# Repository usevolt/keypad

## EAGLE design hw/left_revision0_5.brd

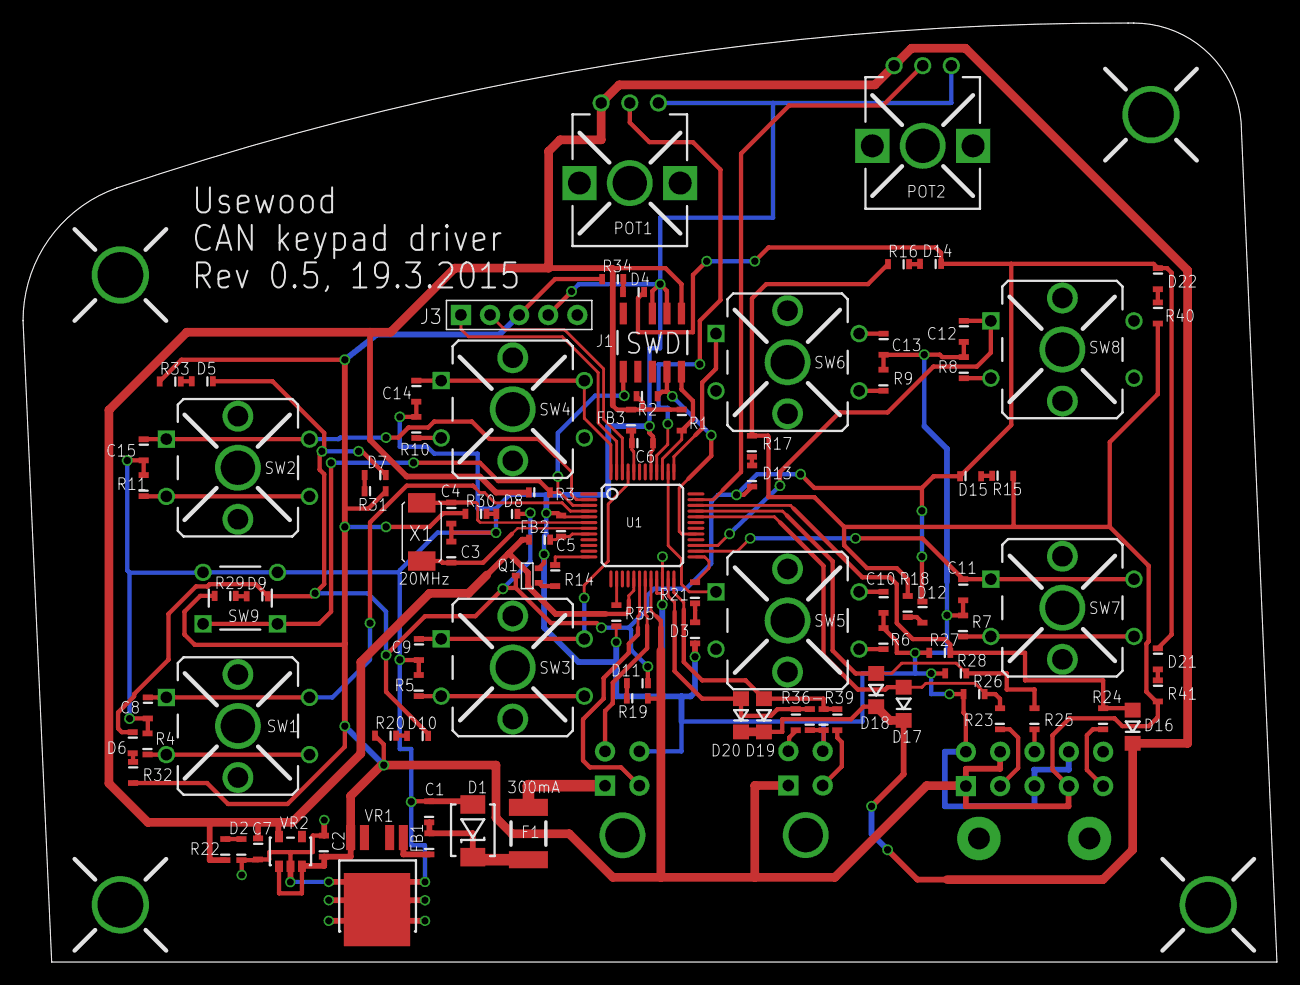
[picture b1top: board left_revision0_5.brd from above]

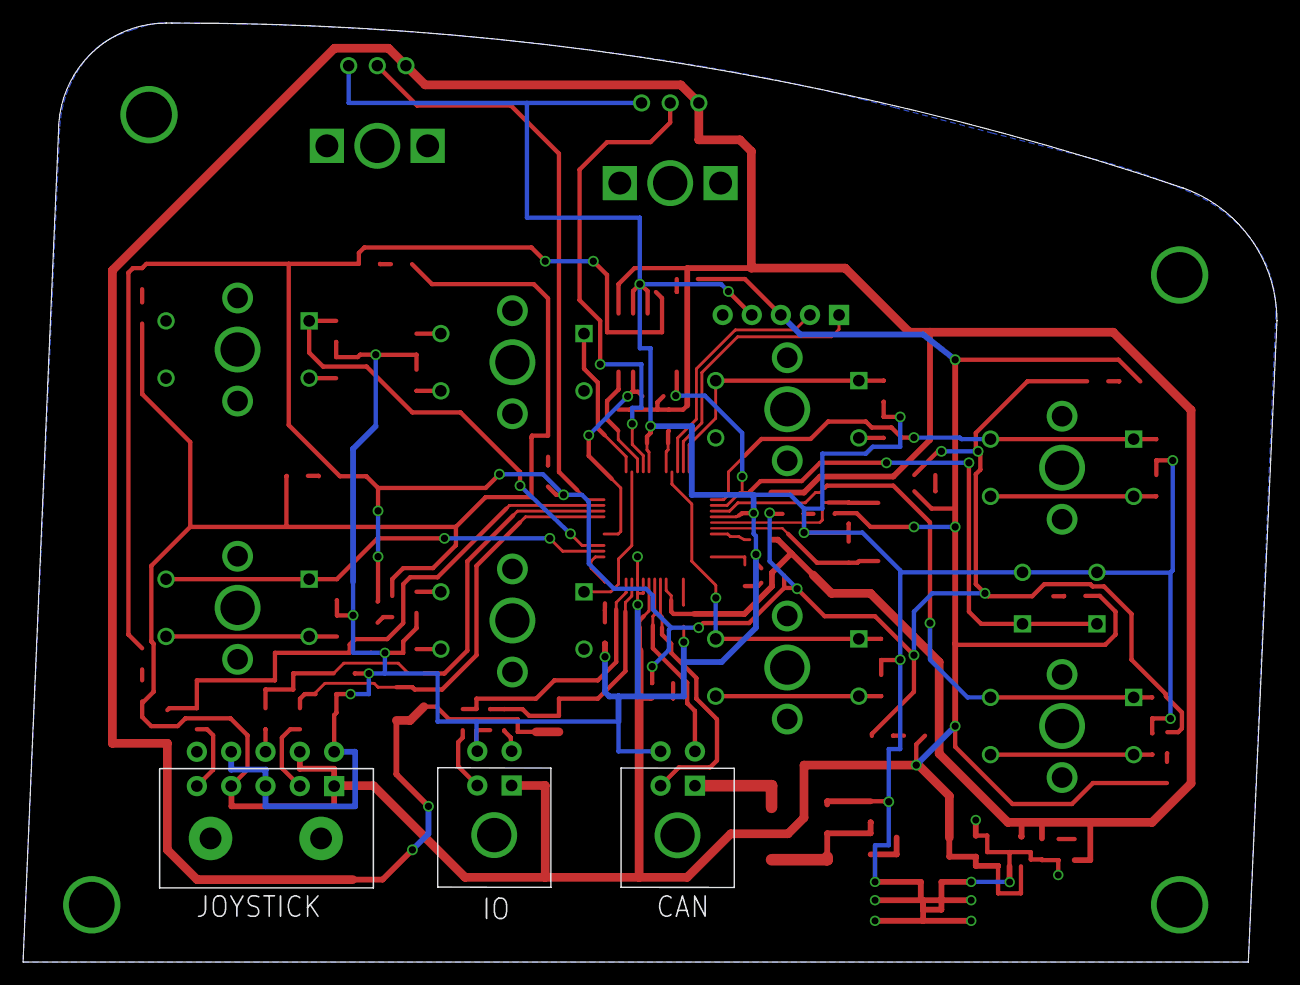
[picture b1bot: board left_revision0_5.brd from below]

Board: 2 copper layers, 109.5 x 82.0 mm, 101 parts (3 on the bottom side), 66 nets.

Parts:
C1, C2, C7: 1u; 0603
C3, C4: 15p; 0603
C5, C6, C8, C9, C10, C11, C12, C13, C14, C15: 100n; 0603
D1: DO-214AB
D2, D3, D4, D5, D6, D7, D8, D9, D10, D11, D12, D13, D14, D15, D21, D22: 0603
D16, D17, D18, D19, D20: DIODEDO219AB; DO219AB
F1: 300mA; FUSE_100MA
FB1, FB2, FB3: FERRITE0603; 0603
J1: SWD; ARM_10_PIN_JTAG/SWD_CONNECTOR
J2: CAN; MOLEX_MICRO-FIT_4WAY
J3: UART; HEADER5_1
J4: IO; MOLEX_MICRO-FIT_4WAY
Q1: SOT323
R1, R2, R3, R23, R24, R25, R36, R37: 10k; 0603
R4, R5, R6, R7, R8, R9, R10, R11: 100; 0603
R12, R13: 10k; RES_POT_RK09K1130C94
R14: 1k; 0603
R15, R16, R17, R18, R19, R20, R21, R29, R30, R31, R32, R33, R34: 470; 0603
R22: 430; 0603
R26, R27, R28, R38, R39: 20k; 0603
R35: 10; 0603
R40, R41: 0603
SW1, SW2, SW3, SW4, SW5, SW6, SW7, SW8: SWITCH_12X12MM_CENTER_HOLE
SW9: SWITCH_REGULAR
U1: QFP48
U$1: JOYSTICK; MOLEX-MICRO-FIT_10WAY
VR1: 175AA
VR2: SOP5
X1: 20MHz; XTAL_SMD_5X3.2

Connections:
+3V3: C7.1, D16.P$2, D17.P$2, D18.P$2, D19.P$2, D20.P$2, FB2.0, FB3.0, J1.P$1, R1.1, R2.1, R3.1, R12.P$3, R13.P$3, R22.1, U1.P$17, VR2.5
+5V: C2.1, J3.P$3, J4.P$1, R15.0, R16.0, R17.0, R18.0, R19.0, R20.0, R29.0, R30.0, R31.0, R32.0, R33.0, R34.0, R40.0, R41.0, U1.P$20, U$1.P$1, U$1.P$4, U$1.P$7, VR1.5, VR2.1, VR2.3
AD0: D17.P$1, R23.0, R26.1, U1.P$32
AD1: D18.P$1, R25.0, R28.1, U1.P$33
AD2: D16.P$1, R24.0, R27.1, U1.P$34
CANH: J2.P$3, U1.P$19
CANL: J2.P$2, U1.P$18
CAN_ISP: R35.0, U1.P$14
GND: C1.0, C2.0, C3.0, C4.0, C5.0, C6.0, C7.0, C8.0, C9.0, C10.0, C11.0, C12.0, C13.0, C14.0, C15.0, D1.P$1, D2.1, D3.1, J1.P$3, J1.P$5, J2.P$4, J3.P$4, J4.P$4, Q1.R, R4.0, R5.0, R6.0, R7.0, R8.0, R9.0, R10.0, R11.0, R12.P$1, R13.P$1, R26.0, R27.0, R28.0, R35.1, R38.1, R39.1, SW9.P$3, SW9.P$4, U1.P$5, U1.P$21, U1.P$22, U1.P$41, U$1.P$3, U$1.P$6, U$1.P$9, VR1.GND, VR2.2
IO1: D20.P$1, R37.1, R38.0, U1.P$23
IO2: D19.P$1, R36.1, R39.0, U1.P$24
LED3: D3.0, R21.1
LED4: D4.0, R34.1
LED5: D5.0, R33.1
LED6: D6.0, R32.1
LED7: D7.0, R31.1
LED8: D8.0, R30.1
LED9: D9.0, R29.1
unnamed: C1.1, D1.P$2, F1.P$2, FB1.0
unnamed: C6.1, FB3.1, U1.P$44
unnamed: D2.0, R22.0
unnamed: FB1.1, VR1.1
unnamed: R14.1, U1.P$12
unnamed: R21.0, U1.P$25
unnamed: R4.1, SW1.P$3, SW1.P$4
unnamed: R5.1, SW3.P$3, SW3.P$4
unnamed: R6.1, SW5.P$3, SW5.P$4
unnamed: R11.1, SW2.P$3, SW2.P$4
unnamed: R9.1, SW6.P$3, SW6.P$4
unnamed: R10.1, SW4.P$3, SW4.P$4
unnamed: R8.1, SW8.P$3, SW8.P$4
unnamed: R7.1, SW7.P$3, SW7.P$4
unnamed: D15.0, R15.1
unnamed: D14.0, R16.1
unnamed: D13.0, R17.1
unnamed: D12.0, R18.1
unnamed: D11.0, R19.1
unnamed: D10.0, R20.1
unnamed: C5.1, FB2.1, U1.P$8
unnamed: J4.P$2, R36.0
unnamed: J4.P$3, R37.0
unnamed: D21.0, R41.1
unnamed: D22.0, R40.1
unnamed: D4.1, D5.1, D6.1, D7.1, D8.1, D9.1, D10.1, D11.1, D12.1, D13.1, D14.1, D15.1, D21.1, D22.1, Q1.M
PIO1_2: R12.P$2, U1.P$40
PIO1_4: R13.P$2, U1.P$35
Q1: Q1.L, R14.0
RESET: J1.P$9, R3.0, SW9.P$1, SW9.P$2, U1.P$3
RXD: J3.P$2, U1.P$46
SW1: C8.1, SW1.P$1, SW1.P$2, U1.P$4
SW2: C15.1, SW2.P$1, SW2.P$2, U1.P$2
SW3: C9.1, SW3.P$1, SW3.P$2, U1.P$45
SW4: C14.1, SW4.P$1, SW4.P$2, U1.P$48
SW5: C10.1, SW5.P$1, SW5.P$2, U1.P$38
SW6: C13.1, SW6.P$1, SW6.P$2, U1.P$37
SW7: C11.1, SW7.P$1, SW7.P$2, U1.P$26
SW8: C12.1, SW8.P$1, SW8.P$2, U1.P$27
SWDCLK: J1.P$4, R2.0, U1.P$29
SWDIO: J1.P$2, R1.0, U1.P$39
TXD: J3.P$1, U1.P$47
VDD: F1.P$1, J2.P$1
XJOY: R23.1, U$1.P$2
XTALIN: C4.1, U1.P$6, X1.P$2
XTALOUT: C3.1, U1.P$7, X1.P$1
YJOY: R24.1, U$1.P$5
ZJOY: R25.1, U$1.P$8

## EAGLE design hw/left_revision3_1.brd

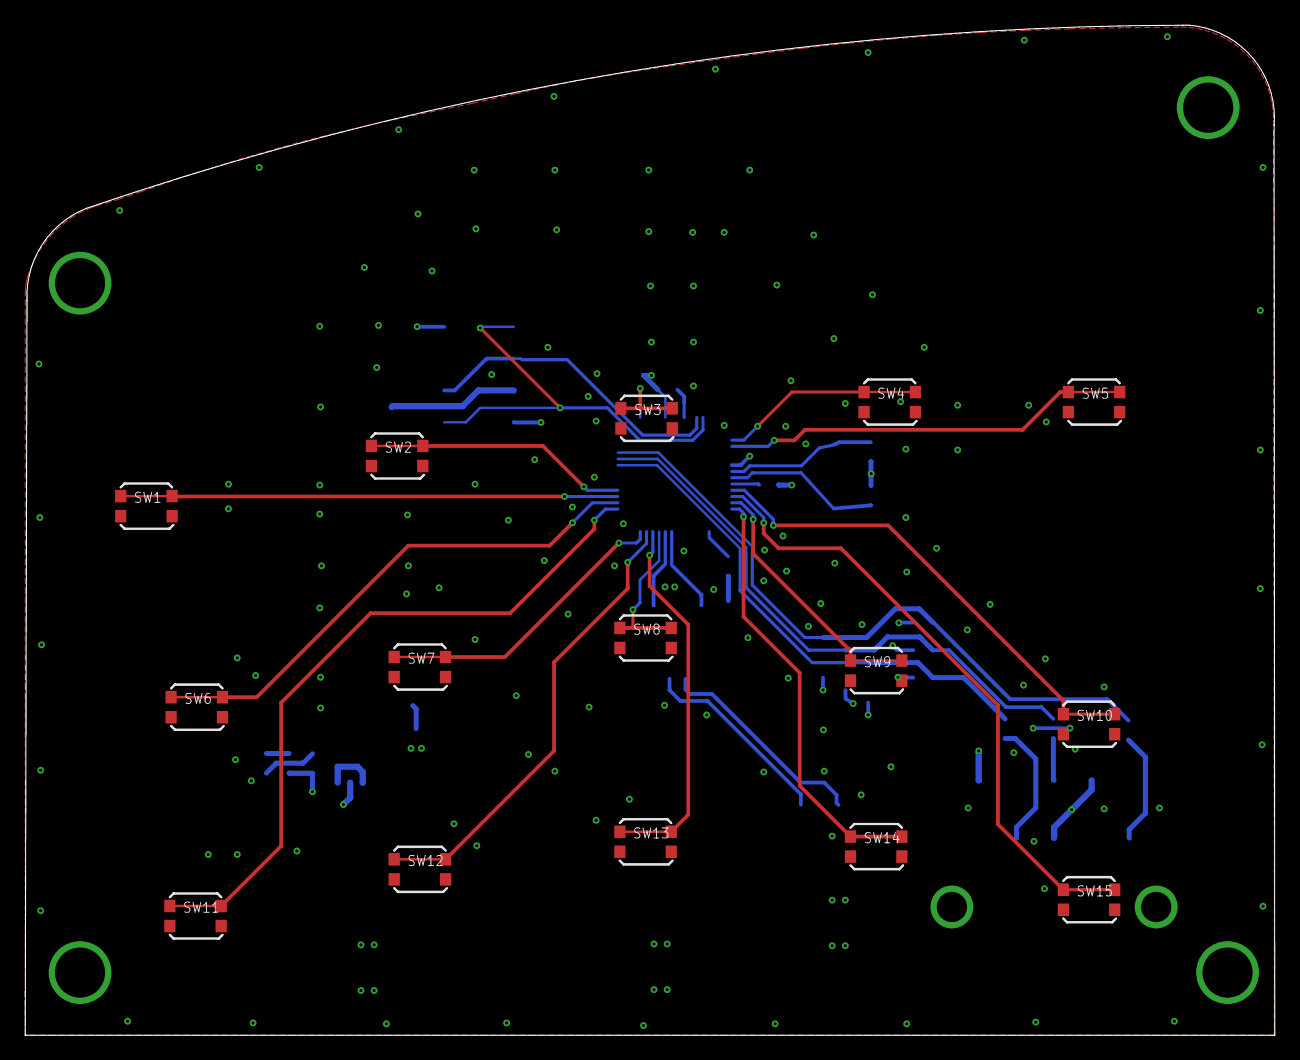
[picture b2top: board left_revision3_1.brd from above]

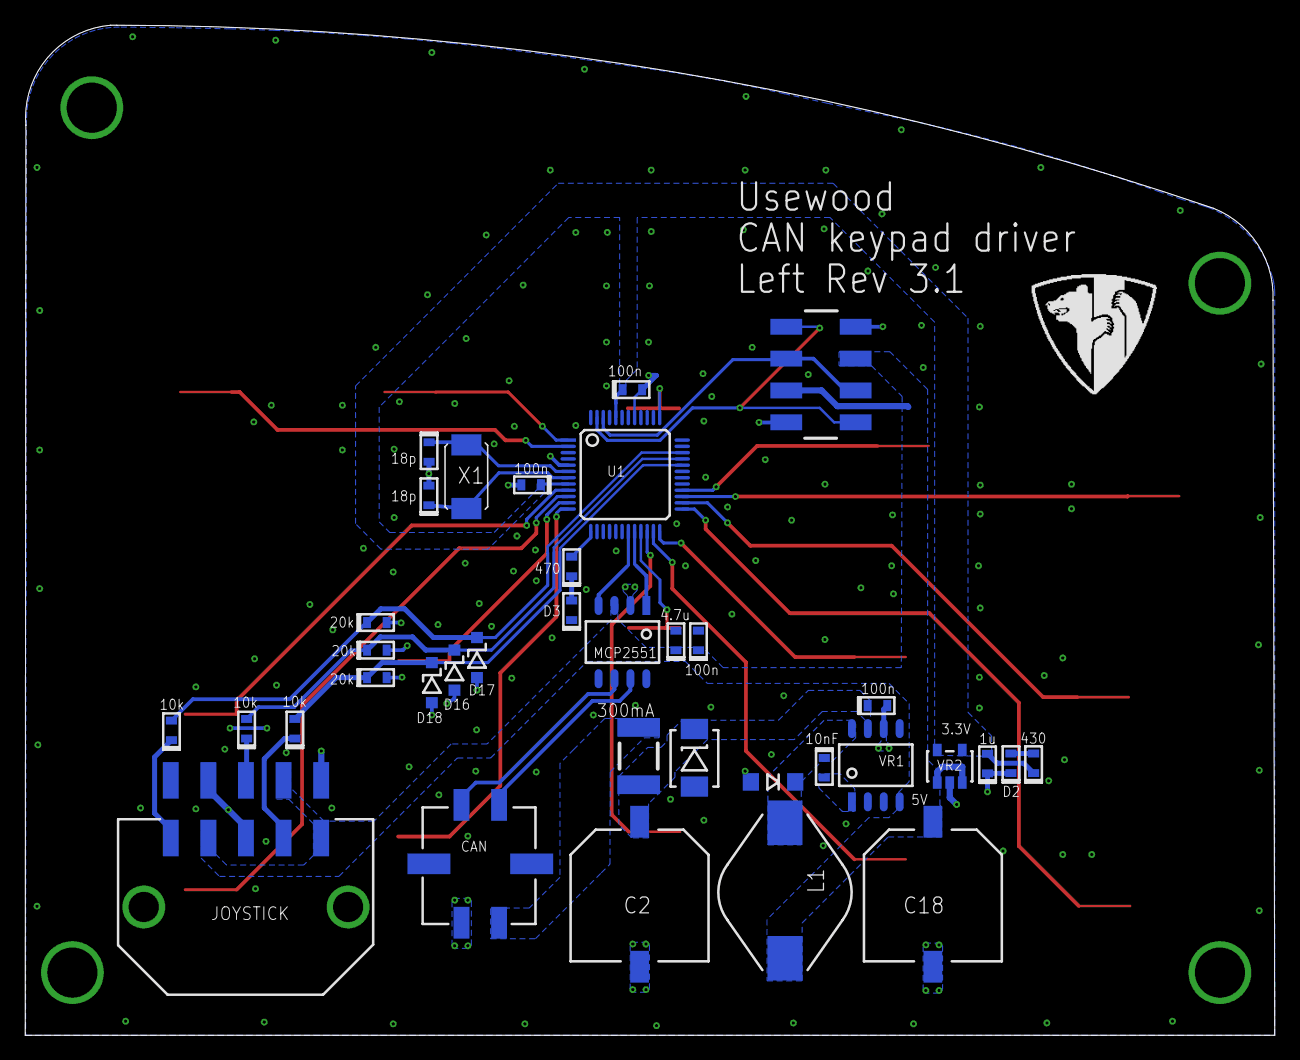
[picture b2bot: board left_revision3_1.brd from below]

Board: 2 copper layers, 99.7 x 80.6 mm, 51 parts (36 on the bottom side), 39 nets.

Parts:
C1, C5, C6, C19: 100n; 0603_SILKSCREEN
C2, C18: EEE1JA101P; CAP_POL_SMD_10X10X10MM
C3, C4: 18p; 0603_SILKSCREEN
C7: 1u; 0603_SILKSCREEN
C16: 4.7u; 0603_SILKSCREEN
C17: 10nF; 0603_SILKSCREEN
D1: DO-214AB
D2, D3: 0603_SILKSCREEN
D16, D17, D18: PDZ3.3B,115; SOD123
D23: RS07J-GS18; DO219AB
F1: 300mA; FUSE_100MA
J1: HEADER_4_2_SMD
J2: CAN; MOLEX_MICRO_FIT_4WAY_SMD
L1: SDR1005-101KL; INDUCTOR_BOURNS_10X13X5MM
R21: 470; 0603_SILKSCREEN
R22: 430; 0603_SILKSCREEN
R23, R24, R25: 10k; 0603_SILKSCREEN
R26, R27, R28: 20k; 0603_SILKSCREEN
SW1, SW2, SW3, SW4, SW5, SW6, SW7, SW8, SW9, SW10, SW11, SW12, SW13, SW14, SW15: SWITCH_KMR231
U1: QFP48
U2: MCP2551; SOIC8
U$1: JOYSTICK; MOLEX_MICRO_FIT_10WAY_SMD
VR1: 5V; SOIC8
VR2: 3.3V; SOP5
X1: 7A-20.000MAAJ-T; XTAL_SMD_5X3.2

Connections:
+3V3: C5.1, C6.1, C7.0, R22.1, U1.P$8, U1.P$44, VR2.5
+5V: C16.1, C18.+, C19.1, J1.P$4, J1.P$5, L1.P$2, U2.P$3, U$1.P$1, U$1.P$4, U$1.P$7, VR1.P$4, VR2.1, VR2.3
AD0: D18.P$2, R23.0, R26.1, U1.P$32
AD1: D16.P$2, R25.0, R28.1, U1.P$33
AD2: D17.P$2, R24.0, R27.1, U1.P$34
CANH: J2.P$3, U2.P$7
CANL: J2.P$4, U2.P$6
GND: C1.0, C2.-, C3.0, C4.0, C5.0, C6.0, C7.1, C16.0, C18.-, C19.0, D1.P$1, D2.1, D3.1, D16.P$1, D17.P$1, D18.P$1, D23.P$1, J1.P$2, J1.P$7, J2.P$2, R26.0, R27.0, R28.0, SW1.P$2, SW1.P$4, SW2.P$2, SW2.P$4, SW3.P$2, SW3.P$4, SW4.P$2, SW4.P$4, SW5.P$2, SW5.P$4, SW6.P$2, SW6.P$4, SW7.P$2, SW7.P$4, SW8.P$2, SW8.P$4, SW9.P$2, SW9.P$4, SW10.P$2, SW10.P$4, SW11.P$2, SW11.P$4, SW12.P$2, SW12.P$4, SW13.P$2, SW13.P$4, SW14.P$2, SW14.P$4, SW15.P$2, SW15.P$4, U1.P$5, U1.P$41, U2.P$2, U2.P$8, U$1.P$3, U$1.P$6, U$1.P$9, VR1.P$6, VR2.2
LED3: D3.0, R21.1
unnamed: R21.0, U1.P$13
unnamed: D2.0, R22.0
unnamed: C1.1, C2.+, D1.P$2, F1.P$2, VR1.P$7
unnamed: U1.P$20, U2.P$1
unnamed: C17.1, D23.P$2, L1.P$1, VR1.P$8
unnamed: U1.P$19, U2.P$4
unnamed: C17.0, VR1.P$1
RXD: J1.P$3, J1.P$6, U1.P$46
SW1: SW1.P$1, SW1.P$3, U1.P$27
SW2: SW2.P$1, SW2.P$3, U1.P$28
SW3: SW3.P$1, SW3.P$3, U1.P$37
SW4: SW4.P$1, SW4.P$3, U1.P$1
SW5: SW5.P$1, SW5.P$3, U1.P$2
SW6: SW6.P$1, SW6.P$3, U1.P$26
SW7: SW7.P$1, SW7.P$3, U1.P$24
SW8: SW8.P$1, SW8.P$3, U1.P$21
SW9: SW9.P$1, SW9.P$3, U1.P$11
SW10: SW10.P$1, SW10.P$3, U1.P$9
SW11: SW11.P$1, SW11.P$3, U1.P$25
SW12: SW12.P$1, SW12.P$3, U1.P$23
SW13: SW13.P$1, SW13.P$3, U1.P$22
SW14: SW14.P$1, SW14.P$3, U1.P$12
SW15: SW15.P$1, SW15.P$3, U1.P$10
TXD: J1.P$1, J1.P$8, U1.P$47
VDD: F1.P$1, J2.P$1
XJOY: R23.1, U$1.P$2
XTALIN: C4.1, U1.P$6, X1.P$2
XTALOUT: C3.1, U1.P$7, X1.P$1
YJOY: R24.1, U$1.P$5
ZJOY: R25.1, U$1.P$8

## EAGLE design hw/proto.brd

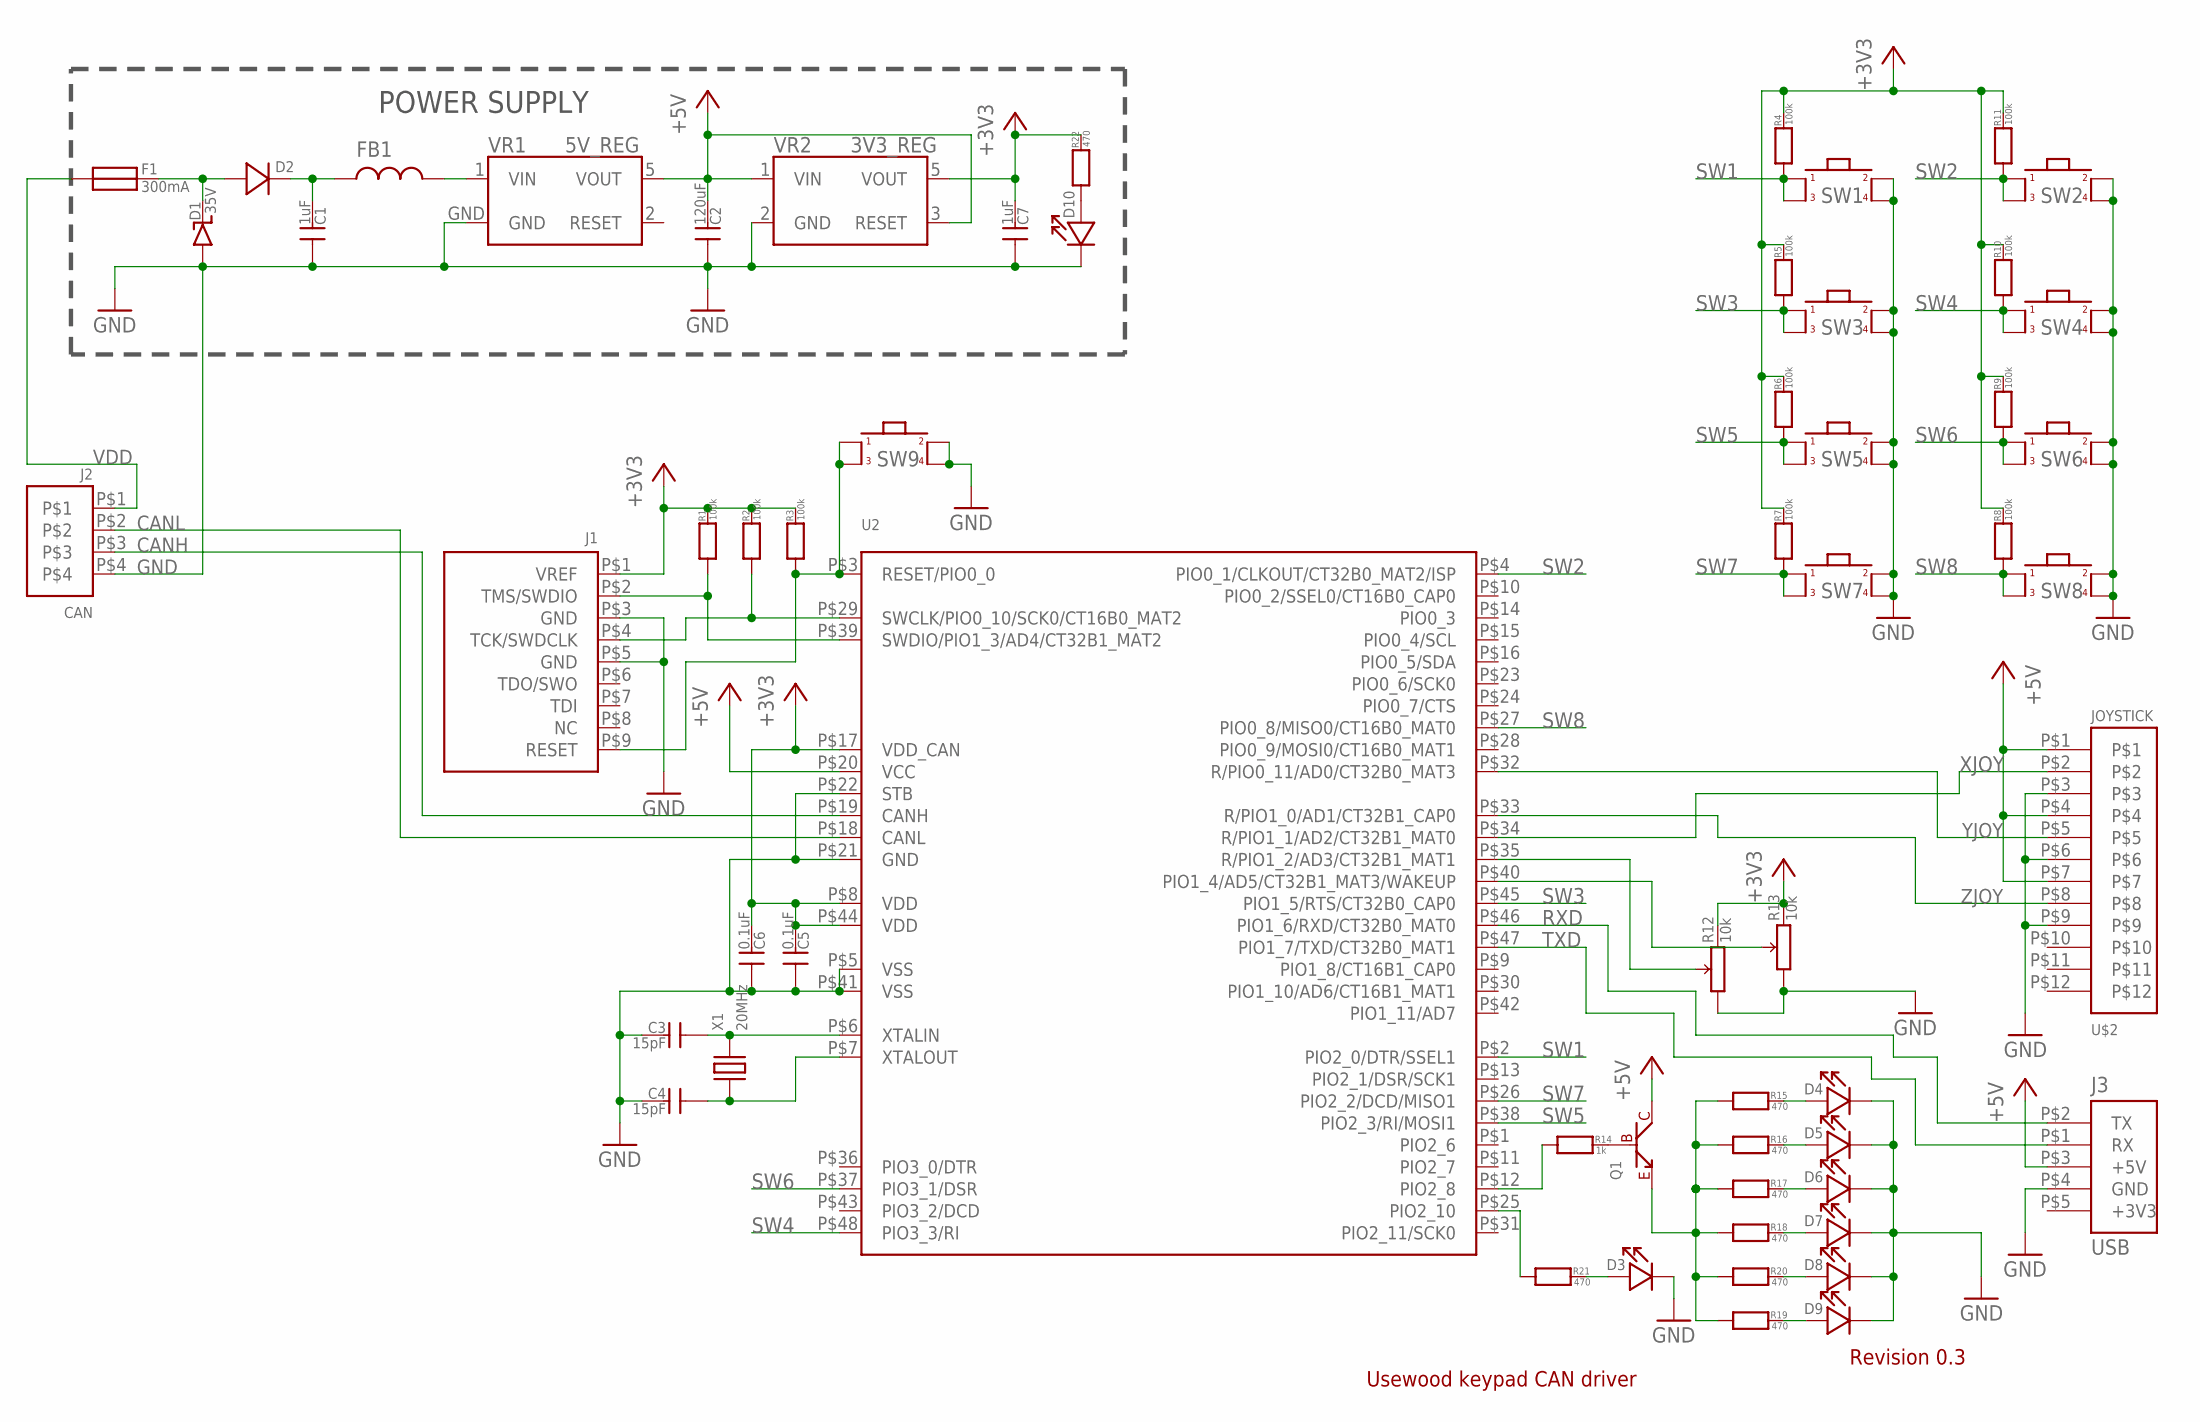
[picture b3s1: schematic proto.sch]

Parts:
C1, C7: 1uF; 0603
C2: 120uF; 0603
C3, C4: 15pF; 0603
C5, C6: 0.1uF; 0603
D1: 35V; DO-214AB
D2: DIODEDO219AB; DO219AB
D3, D4, D5, D6, D7, D8, D9, D10: LED0603; 0603
F1: 300mA; FUSE_100MA
FB1: FERRITE0603; 0603
J1: ARM_JTAG/SWD_HEADER_10_PINSMD; ARM_10_PIN_JTAG/SWD_CONNECTOR
J2: CAN; MOLEX_MICRO-FIT_4WAY
J3: USB; HEADER5_1
Q1: NPN_TRANSISTORSOT323; SOT323
R1, R2, R3, R4, R5, R6, R7, R8, R9, R10, R11: 100k; 0603
R12, R13: 10k; RES_POT_RK09K1130C94
R14: 1k; 0603
R15, R16, R17, R18, R19, R20, R21, R22: 470; 0603
SW1, SW2, SW3, SW4, SW5, SW6, SW7, SW8: SWITCH12X12MM_CENTER_HOLE; SWITCH_12X12MM_CENTER_HOLE
SW9: SWITCHREGULAR; SWITCH_REGULAR
U2: LPC11C22QFP48; QFP48
U$2: JOYSTICK; MOLEX-43045-1000
VR1: 5V_REG; 175AA
VR2: 3V3_REG; SOP5
X1: 20MHz; XTAL_SMD_5X3.2

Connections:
+3V3: C5.1, C6.1, C7.1, J1.P$1 (VREF), R1.1, R2.1, R3.1, R4.1, R5.1, R6.1, R7.1, R8.1, R9.1, R10.1, R11.1, R12.P$3, R13.P$3, R22.1, U2.P$8 (VDD), U2.P$17 (VDD_CAN), U2.P$44 (VDD), VR2.5 (VOUT)
+5V: C2.1, J3.P$3 (+5V), Q1.M (C), U2.P$20 (VCC), U$2.P$1, U$2.P$4, U$2.P$7, VR1.5 (VOUT), VR2.1 (VIN), VR2.3 (RESET)
CANH: J2.P$3, U2.P$19 (CANH)
CANL: J2.P$2, U2.P$18 (CANL)
GND: C1.0, C2.0, C3.1, C4.1, C5.0, C6.0, C7.0, D1.P$1, D3.1, D4.1, D5.1, D6.1, D7.1, D8.1, D9.1, D10.1, J1.P$3 (GND), J1.P$5 (GND), J2.P$4, J3.P$4 (GND), R12.P$1, R13.P$1, SW1.P$3, SW1.P$4, SW2.P$3, SW2.P$4, SW3.P$3, SW3.P$4, SW4.P$3, SW4.P$4, SW5.P$3, SW5.P$4, SW6.P$3, SW6.P$4, SW7.P$3, SW7.P$4, SW8.P$3, SW8.P$4, SW9.P$3, SW9.P$4, U2.P$5 (VSS), U2.P$21 (GND), U2.P$22 (STB), U2.P$41 (VSS), U$2.P$3, U$2.P$6, U$2.P$9, VR1.GND, VR2.2 (GND)
LED3: D3.0, R21.1
LED4: D4.0, R15.1
LED5: D5.0, R16.1
LED6: D6.0, R17.1
LED7: D7.0, R18.1
LED8: D8.0, R20.1
LED9: D9.0, R19.1
unnamed: D1.P$2 (N), D2.P$1, F1.P$2
unnamed: C1.1, D2.P$2 (N), FB1.0
unnamed: D10.0, R22.0
unnamed: FB1.1, VR1.1 (VIN)
unnamed: R14.0, U2.P$12 (PIO2_8)
unnamed: R21.0, U2.P$25 (PIO2_10)
unnamed: Q1.R (E), R15.0, R16.0, R17.0, R18.0, R19.0, R20.0
PIO1_2: R13.P$2, U2.P$40 (PIO1_4/AD5/CT32B1_MAT3/WAKEUP)
PIO1_4: R12.P$2, U2.P$35 (R/PIO1_2/AD3/CT32B1_MAT1)
Q1: Q1.L (B), R14.1
RESET: J1.P$9 (RESET), R3.0, SW9.P$1, SW9.P$2, U2.P$3 (RESET/PIO0_0)
RXD: J3.P$2 (TX), U2.P$46 (PIO1_6/RXD/CT32B0_MAT0)
SW1: R4.0, SW1.P$1, SW1.P$2, U2.P$2 (PIO2_0/DTR/SSEL1)
SW2: R11.0, SW2.P$1, SW2.P$2, U2.P$4 (PIO0_1/CLKOUT/CT32B0_MAT2/ISP)
SW3: R5.0, SW3.P$1, SW3.P$2, U2.P$45 (PIO1_5/RTS/CT32B0_CAP0)
SW4: R10.0, SW4.P$1, SW4.P$2, U2.P$48 (PIO3_3/RI)
SW5: R6.0, SW5.P$1, SW5.P$2, U2.P$38 (PIO2_3/RI/MOSI1)
SW6: R9.0, SW6.P$1, SW6.P$2, U2.P$37 (PIO3_1/DSR)
SW7: R7.0, SW7.P$1, SW7.P$2, U2.P$26 (PIO2_2/DCD/MISO1)
SW8: R8.0, SW8.P$1, SW8.P$2, U2.P$27 (PIO0_8/MISO0/CT16B0_MAT0)
SWDCLK: J1.P$4 (TCK/SWDCLK), R2.0, U2.P$29 (SWCLK/PIO0_10/SCK0/CT16B0_MAT2)
SWDIO: J1.P$2 (TMS/SWDIO), R1.0, U2.P$39 (SWDIO/PIO1_3/AD4/CT32B1_MAT2)
TXD: J3.P$1 (RX), U2.P$47 (PIO1_7/TXD/CT32B0_MAT1)
VDD: F1.P$1, J2.P$1
XJOY: U2.P$34 (R/PIO1_1/AD2/CT32B1_MAT0), U$2.P$2
XTALIN: C3.0, U2.P$6 (XTALIN), X1.P$2
XTALOUT: C4.0, U2.P$7 (XTALOUT), X1.P$1
YJOY: U2.P$32 (R/PIO0_11/AD0/CT32B0_MAT3), U$2.P$5
ZJOY: U2.P$33 (R/PIO1_0/AD1/CT32B1_CAP0), U$2.P$8

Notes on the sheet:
Usewood keypad CAN driver
Revision 0.3
POWER SUPPLY

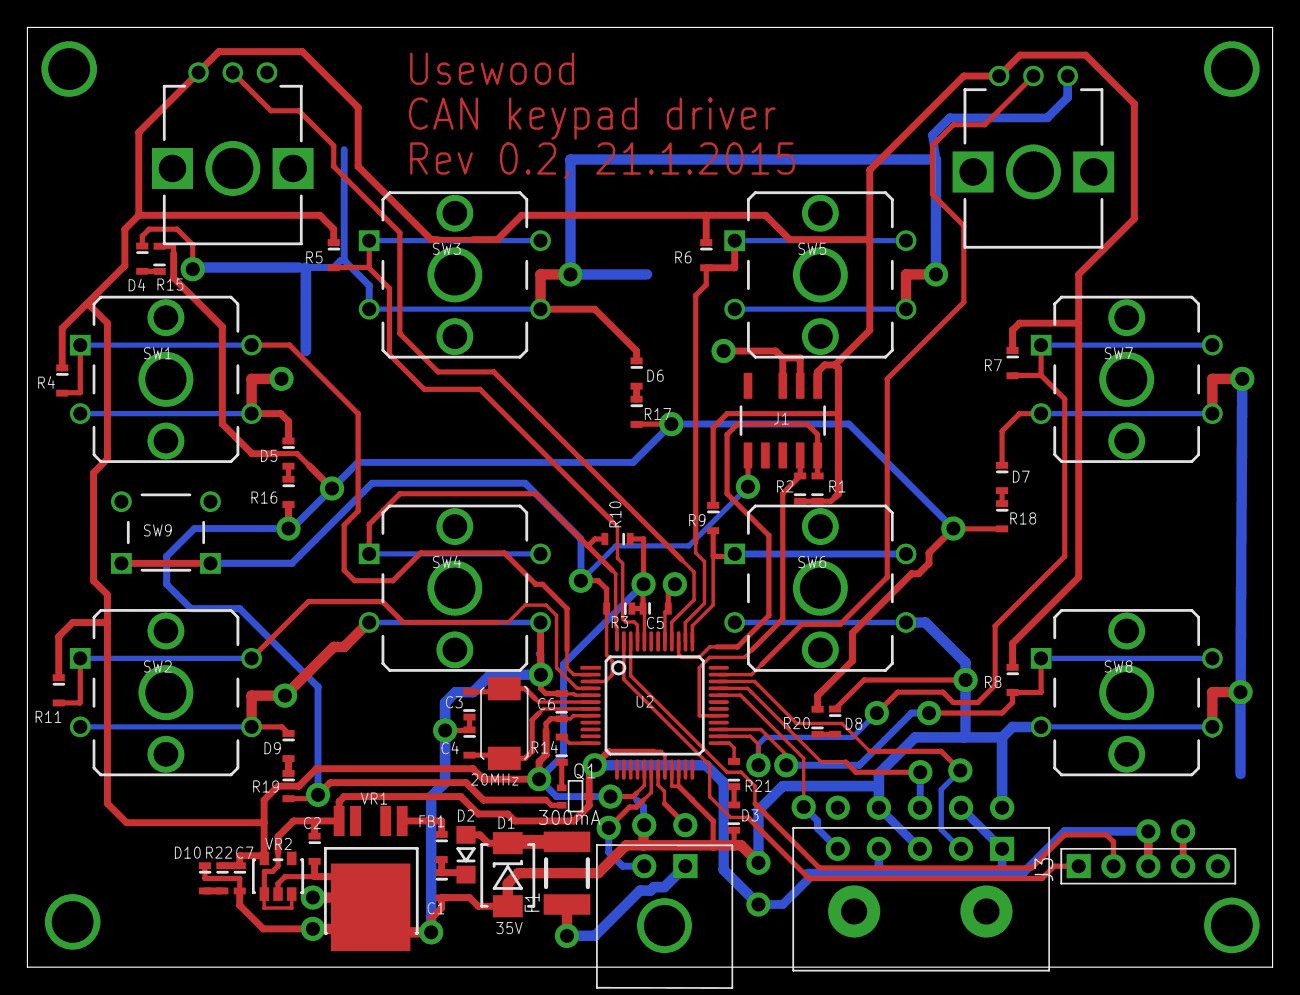
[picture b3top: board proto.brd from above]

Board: 2 copper layers, 90.9 x 68.6 mm, 59 parts (0 on the bottom side), 41 nets.
